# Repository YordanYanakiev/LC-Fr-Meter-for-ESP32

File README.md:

# LC-Fr-Meter-for-ESP32
V1 of LC+Resonance Frequency Meter for ESP32

 I've searched for a while for ESP32 based LC ( Induction / Capacitance ) meter but seems like everyone were arduino based.
So.. I've created one which actually looks better than the rest ;)
It's based on LM393N but You could replace it with similar.
In the github - you can get the full EAGLE PCB single layer optimized board and the circuit with a few libraries which I've created as well, and the demo project.
ENJOY ! :) ...

*** NOTE that as better the quality and smaller is the tolerance of the capacitor - the better readings you will get.
*** It is used 10 nF 10% capacitor. If You have other one, or you need to measure higher or lower inductances - change the capacitor, and reflect it's changes inside the code.

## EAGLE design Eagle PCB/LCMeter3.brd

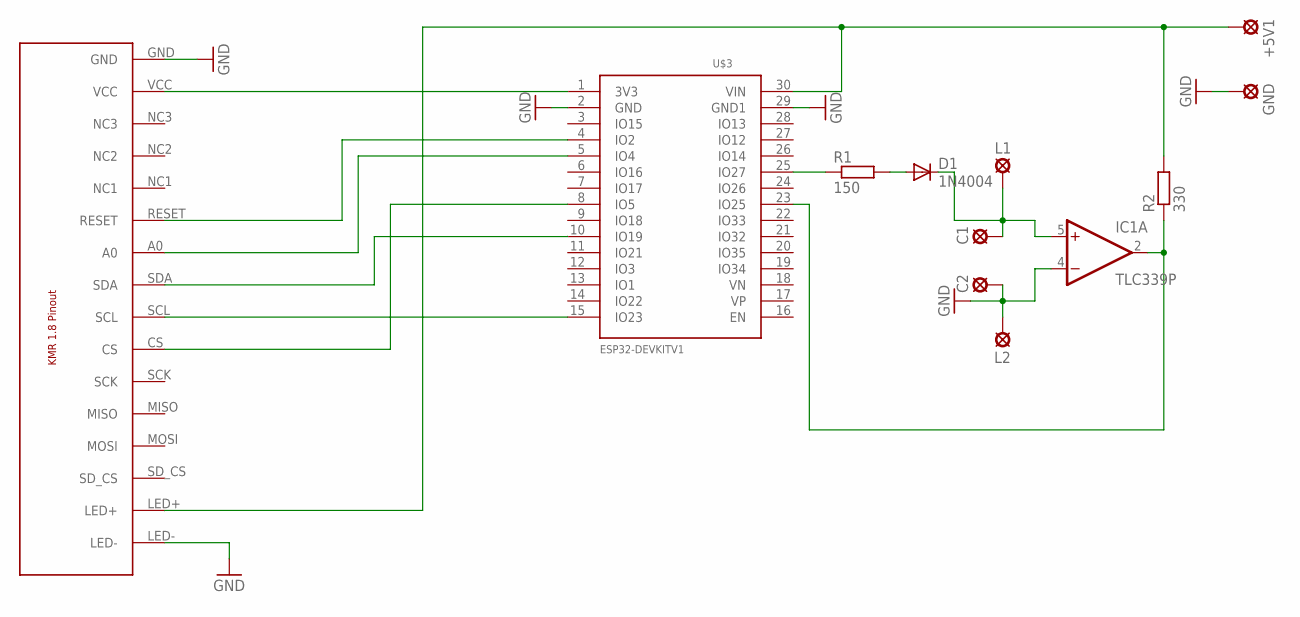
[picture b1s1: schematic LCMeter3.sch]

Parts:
+5V1: LSP10
C1, C2: LSP10
D1: 1N4004; DO41-10
GND: LSP10
IC1: TLC339P; DIL14
L1, L2: LSP10
R1: 150; 0207/10
R2: 330; 0207/10
U$3: ESP32DEVKITV1; ESP32-DEVKITV1
U$4: KMR-1.8

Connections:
GND: C2.MP, GND.MP, IC1.4 (-IN), IC1.12 (GND), L2.MP, U$3.2 (GND), U$3.29 (GND1), U$4.GND, U$4.LED-
unnamed: D1.A, R1.2
unnamed: C1.MP, D1.C, IC1.5 (+IN), L1.MP
unnamed: R1.1, U$3.25 (IO27)
unnamed: IC1.2 (OUT), R2.1, U$3.23 (IO25)
unnamed: U$3.1 (3V3), U$4.VCC
unnamed: U$3.15 (IO23), U$4.SCL
unnamed: U$3.10 (IO19), U$4.SDA
unnamed: U$3.8 (IO5), U$4.CS
unnamed: U$3.5 (IO4), U$4.A0
unnamed: U$3.4 (IO2), U$4.RESET
V+: +5V1.MP, IC1.3 (V+), R2.2, U$3.30 (VIN), U$4.LED+

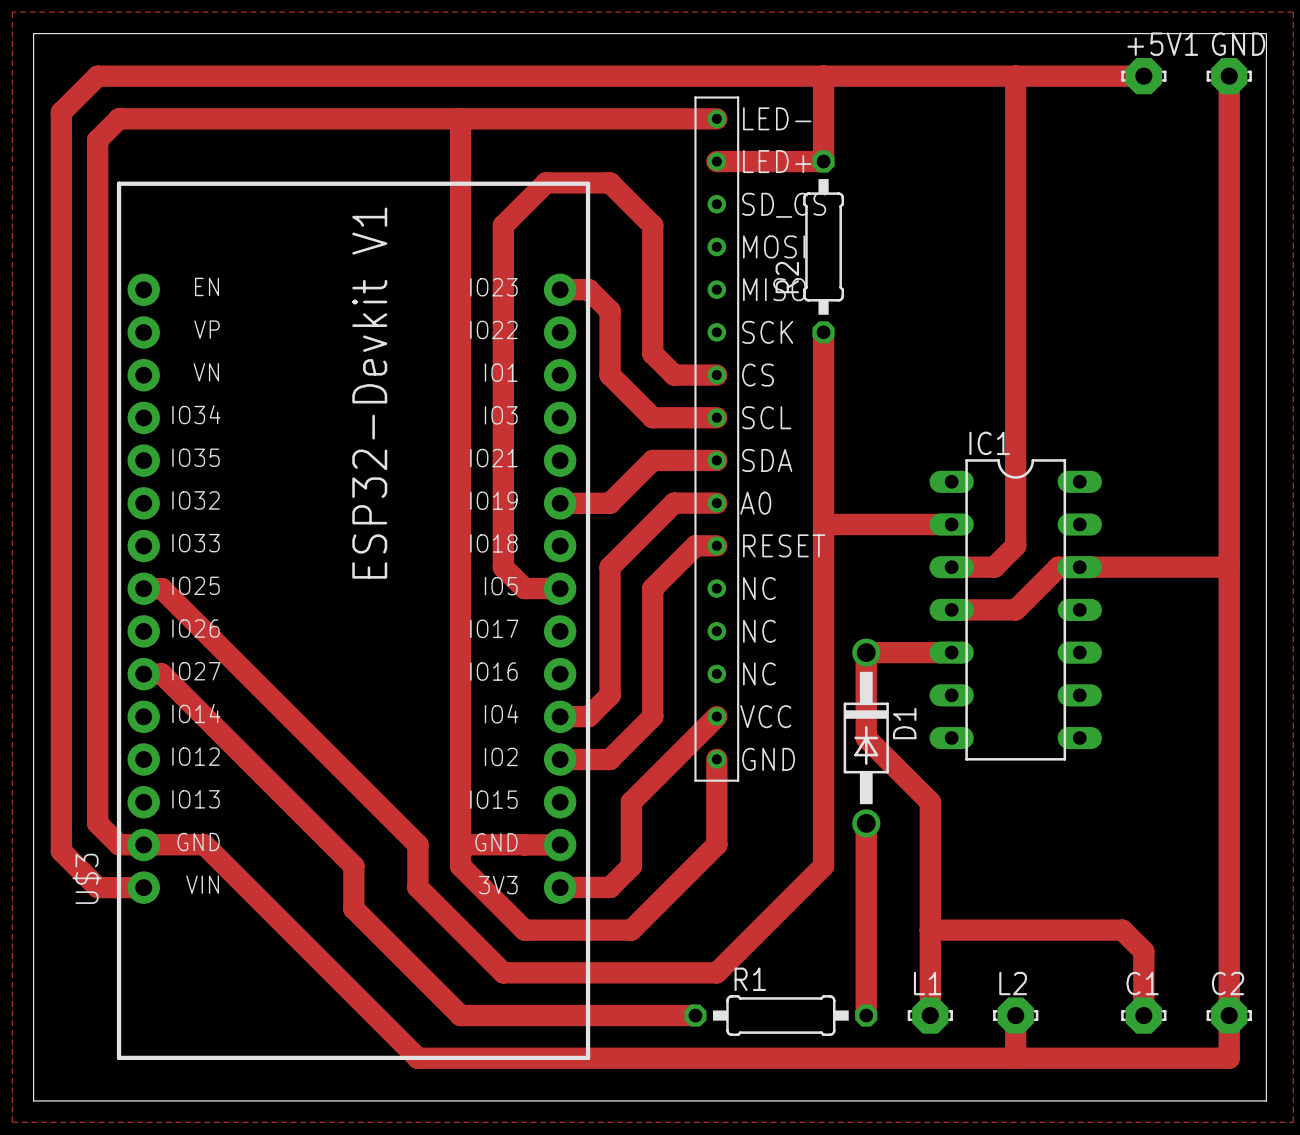
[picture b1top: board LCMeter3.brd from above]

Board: 2 copper layers, 73.3 x 63.5 mm, 12 parts (0 on the bottom side), 12 nets.
